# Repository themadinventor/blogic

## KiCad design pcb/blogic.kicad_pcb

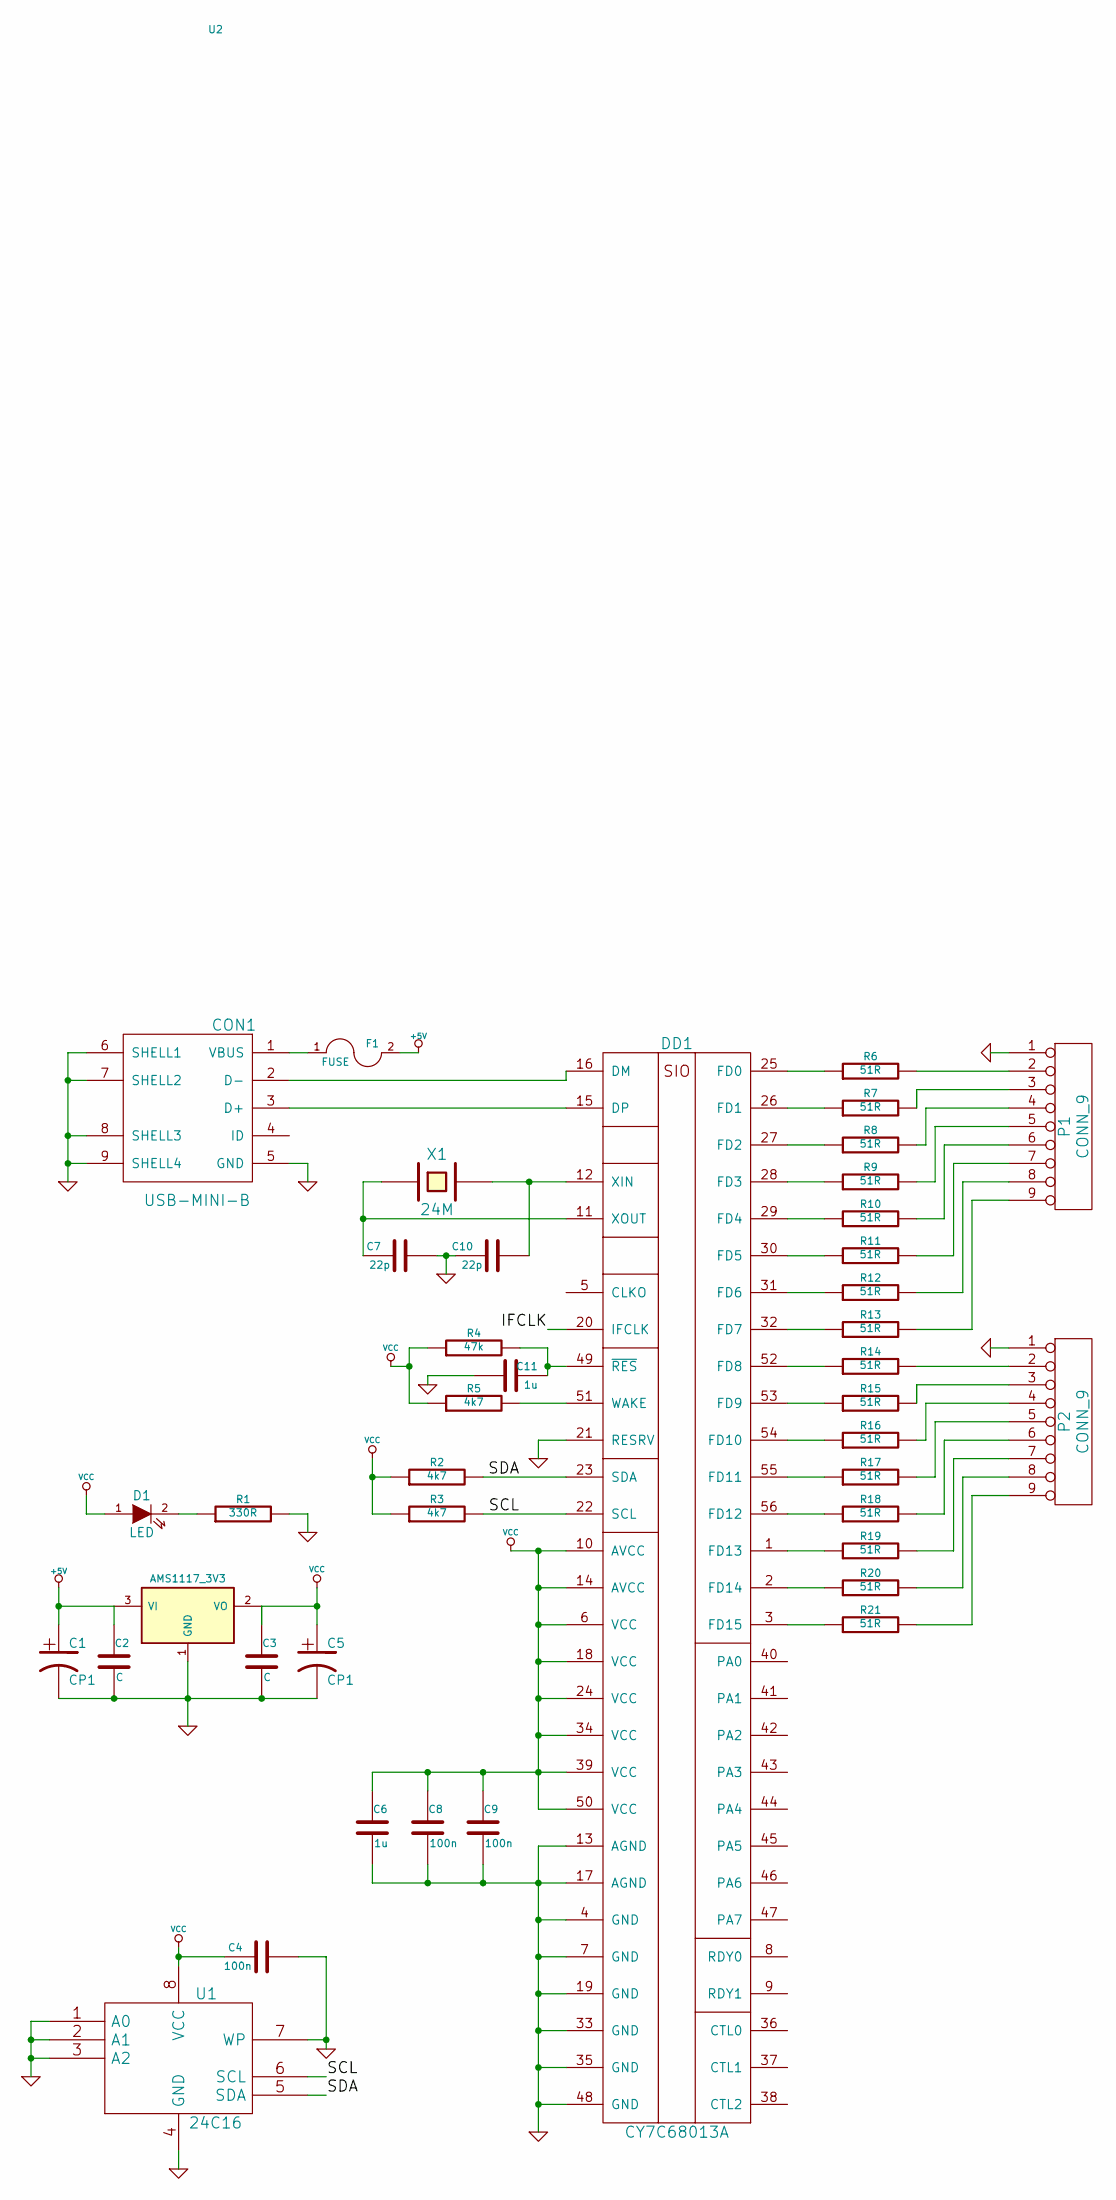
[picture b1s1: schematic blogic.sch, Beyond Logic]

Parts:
C1, C5: CP1
C2, C3: C
C4, C8, C9: 100n
C6, C11: 1u
C7, C10: 22p
CON1: USB-MINI-B
D1: LED
DD1: CY7C68013A
F1: FUSE
P1, P2: CONN_9
R1: 330R
R2, R3, R5: 4k7
R4: 47k
R6, R7, R8, R9, R10, R11, R12, R13, R14, R15, R16, R17, R18, R19, R20, R21: 51R
U1: 24C16
U2: AMS1117_3V3
X1: 24M

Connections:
+5V: C1.1, C2.1, F1.2, U2.3 (VI)
/SCL: DD1.22 (SCL), R3.2, U1.6 (SCL)
/SDA: DD1.23 (SDA), R2.2, U1.5 (SDA)
GND: C1.2, C2.2, C3.2, C4.2, C5.2, C6.2, C7.2, C8.2, C9.2, C10.1, C11.1, CON1.5 (GND), CON1.6 (SHELL1), CON1.7 (SHELL2), CON1.8 (SHELL3), CON1.9 (SHELL4), DD1.4 (GND), DD1.7 (GND), DD1.13 (AGND), DD1.17 (AGND), DD1.19 (GND), DD1.21 (RESRV), DD1.33 (GND), DD1.35 (GND), DD1.48 (GND), P1.1, P2.1, R1.2, U1.1 (A0), U1.2 (A1), U1.3 (A2), U1.4 (GND), U1.7 (WP), U2.1 (GND)
unnamed: DD1.26 (FD1), R7.1
unnamed: DD1.25 (FD0), R6.1
unnamed: DD1.27 (FD2), R8.1
unnamed: DD1.52 (FD8), R14.1
unnamed: DD1.2 (FD14), R20.1
unnamed: DD1.1 (FD13), R19.1
unnamed: DD1.56 (FD12), R18.1
unnamed: DD1.55 (FD11), R17.1
unnamed: DD1.54 (FD10), R16.1
unnamed: DD1.53 (FD9), R15.1
unnamed: P2.2, R14.2
unnamed: DD1.32 (FD7), R13.1
unnamed: DD1.31 (FD6), R12.1
unnamed: DD1.30 (FD5), R11.1
unnamed: DD1.29 (FD4), R10.1
unnamed: DD1.28 (FD3), R9.1
unnamed: CON1.3 (D+), DD1.15 (DP)
unnamed: CON1.1 (VBUS), F1.1
unnamed: P2.8, R20.2
unnamed: CON1.2 (D-), DD1.16 (DM)
unnamed: P2.7, R19.2
unnamed: P2.6, R18.2
unnamed: P2.5, R17.2
unnamed: P2.4, R16.2
unnamed: P2.3, R15.2
unnamed: P1.9, R13.2
unnamed: P1.8, R12.2
unnamed: P1.7, R11.2
unnamed: D1.2 (K), R1.1
unnamed: P2.9, R21.2
unnamed: P1.6, R10.2
unnamed: P1.5, R9.2
unnamed: P1.4, R8.2
unnamed: P1.3, R7.2
unnamed: P1.2, R6.2
unnamed: DD1.3 (FD15), R21.1
unnamed: C7.1, DD1.11 (XOUT), X1.1
unnamed: C11.2, DD1.49 (~RES), R4.2
unnamed: DD1.51 (WAKE), R5.2
unnamed: C10.2, DD1.12 (XIN), X1.2
VCC: C3.1, C4.1, C5.1, C6.1, C8.1, C9.1, D1.1 (A), DD1.6 (VCC), DD1.10 (AVCC), DD1.14 (AVCC), DD1.18 (VCC), DD1.24 (VCC), DD1.34 (VCC), DD1.39 (VCC), DD1.50 (VCC), R2.1, R3.1, R4.1, R5.1, U1.8 (VCC), U2.2 (VO)

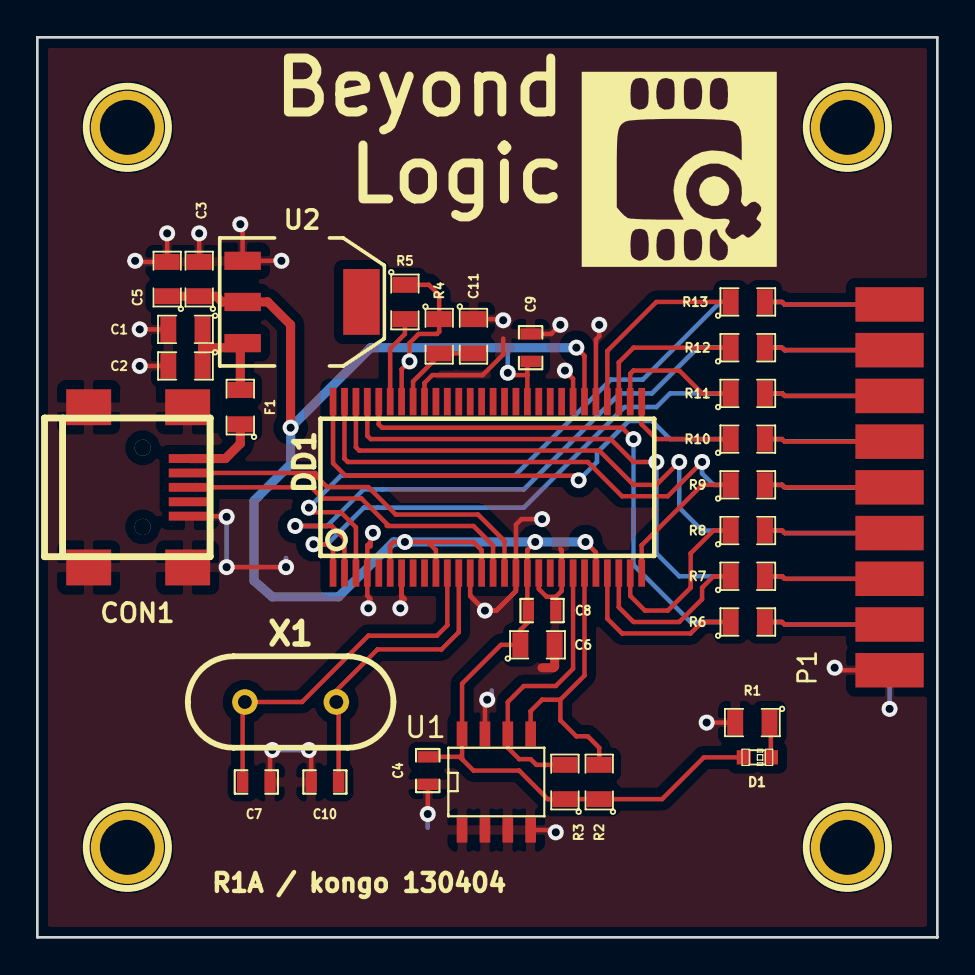
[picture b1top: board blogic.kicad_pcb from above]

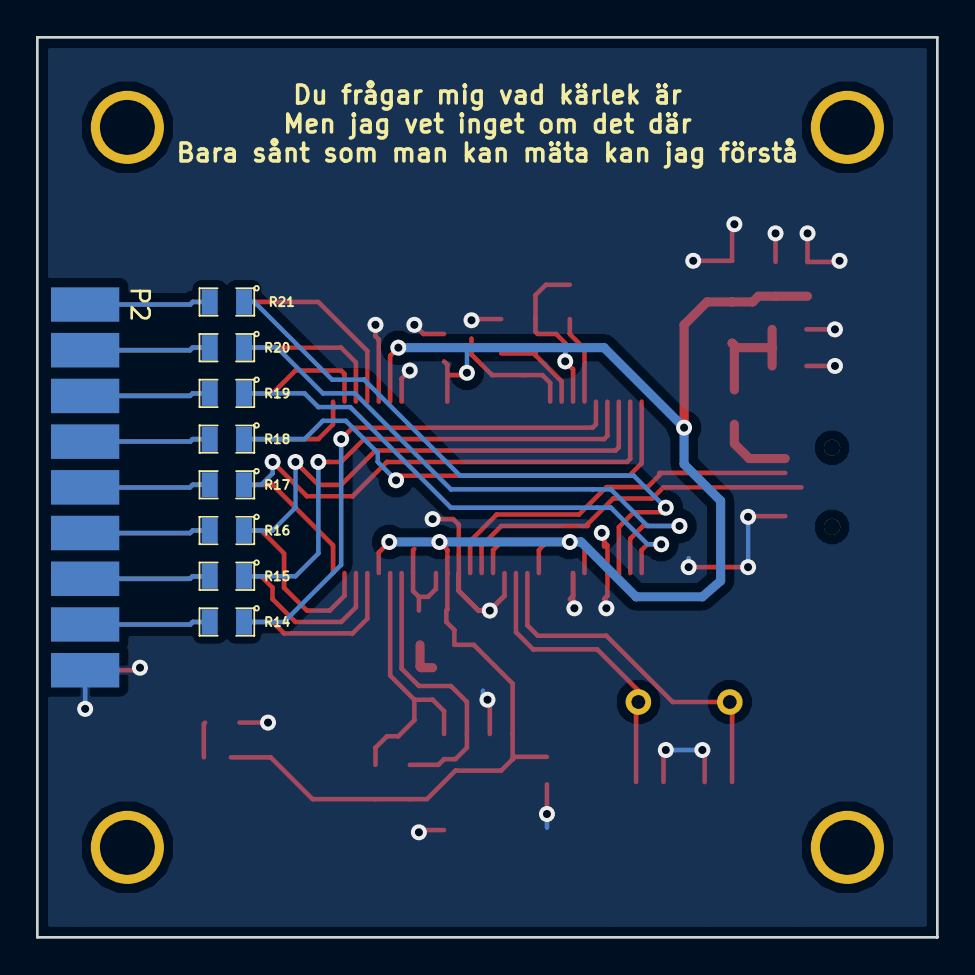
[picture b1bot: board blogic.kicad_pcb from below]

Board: 2 copper layers, 50.0 x 50.0 mm, 45 parts (9 on the bottom side), 45 nets.

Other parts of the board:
1PIN, 1PIN#2, 1PIN#3, 1PIN#4: P***; 1pin

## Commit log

2013-04-01 init
2013-04-17 gerber
2013-04-17 move
2013-04-17 schematic as pdf
2013-04-17 firmware tools
2013-11-02 cleanup
